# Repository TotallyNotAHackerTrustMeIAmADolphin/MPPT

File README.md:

# MPPT Controller - STM32F072 Firmware

A professional-grade firmware for a Maximum Power Point Tracking (MPPT) solar charge controller, optimized for the **ARM Cortex-M0** architecture. This project implements high-frequency power conversion with advanced sensing, robust safety, and optimized regulation logic.

---

## 🚀 Key Technical Features

### 1. High-Frequency PWM with Resolution Dithering
- **Frequency:** 200 kHz switching frequency for high power density.
- **Dithering:** Implements a **4-bit dithering table** (16 cycles). This effectively increases the PWM resolution from 240 steps to **3840 steps**, allowing for ultra-fine-grained voltage and current control.
- **Hardware Integration:** Managed via TIM1 with DMA-based automated duty cycle updates.

### 2. High-Performance Sensing (Ping-Pong ADC)
- **Zero-Latency DMA:** Uses circular DMA to sample 6 analog channels continuously.
- **Double Buffering:** Implements industry-standard **Ping-Pong buffering**. The CPU processes one half of the sample buffer while the DMA fills the other half, eliminating data tearing and race conditions.
- **Channels:** Input Voltage, Output Voltage, Input Current, Output Current, MOSFET Temperature, and MCU Internal Temperature.

### 3. Optimized Math Engine (Semantic Fixed-Point)
- **No FPU overhead:** Designed specifically for the STM32F0 (which lacks a hardware Floating Point Unit). All calculations use high-speed 32-bit and 64-bit integer arithmetic.
- **Unit Precision:** 
  - **Voltages:** Millivolts (`_mV`)
  - **Currents:** Milliamps (`_mA`)
  - **Power:** Microwatts (`_uW`)
  - **PWM:** Raw Dithered Ticks (`_ticks`)

### 4. Sunlight-Readable Telemetry Display
- **Hardware:** Integrated **Nokia 5110 (PCD8544)** LCD via SPI1.
- **Performance:** Non-blocking 10Hz UI refresh task decoupled from high-rate power control.
- **UI Design:** Real-time monitoring of Vin, Vout, Pout, and Operation Mode with vertical decimal alignment for high readability.

### 5. Advanced Control & Safety Logic
- **Velocity PI Regulation:** Implements a mathematically stable **Velocity PI algorithm** for Constant Voltage (CV) and Constant Current (CC) modes. This eliminates double-integration instability and provides rock-solid, ripple-free regulation.
- **Limit-Aware MPPT (P&O):** A refined Perturb & Observe algorithm with **power accumulation logic**. It accurately tracks the maximum power point on gentle slopes and intelligently "parks" the duty cycle near user limits to prevent state flapping.
- **Stabilized Global Sweep:** Slowed-down global sweep (15s duration) ensures hardware capacitors settle, providing a near-perfect MPP baseline without voltage offsets.
- **Hardware Safety Architecture:** Dedicated protection layer for the board:
  - **Over-Voltage:** 80V (Vin), 60V (Vout).
  - **Over-Current:** 20A (Input/Output).
  - **Under-Voltage:** 12.5V (Vin) floor to protect auxiliary power.
  - **Thermal:** 85°C internal limit.
  - **Reverse Flow:** Active backflow detection from battery to panel.

---

## 🛠 Hardware & Platform

### Board: openMPPT v1.1 (Custom Architecture)

- **MCU:** STM32F072RBT6 (ARM Cortex-M0 @ 48MHz).
- **Topology:** 4-Switch Synchronous Non-Inverting Buck-Boost.
- **Power Stage:** Four TI **CSD19505KCS** 80V N-Channel MOSFETs driven by two Infineon **IRS21867STRPBF** gate drivers. High-side drivers are powered by isolated **B1212S-1W** DC-DC converters for continuous high-voltage operation.
- **Sensing:** Precision zero-drift **INA240A4DR** current sense amplifiers. *(Note: Footprints for isolated ACS712 sensors exist as a planned future replacement for the INA240).*
- **Auxiliary Power:** **XL7005A** wide-input buck converters providing 12V and 3.3V logic rails from panel voltage.
- **Display:** Integrated **Nokia 5110 LCD** for real-time telemetry (SPI1).
- **Framework:** STM32Cube HAL.
- **Build System:** PlatformIO using a custom `openmppt` board definition.
- **Headless Operation:** The board regulates autonomously without requiring a serial connection.

---

## 🏗 Build & Development Workflow

### Requirements
- [PlatformIO Core](https://platformio.org/)
- STM32CubeMX (optional, for peripheral reconfiguration)

### Custom Build Automation
This project uses a custom script, `setup_cubemx_env_auto.py`, which bridges the gap between STM32CubeMX and PlatformIO.
- **Automatic Constant Extraction:** The script automatically reads your PWM frequency and timer settings directly from the `MPPT.ioc` file at compile-time.
- **Link Management:** Automatically handles library linking for USB and HAL drivers.

### Commands
```bash
# Build the firmware
pio run

# Upload via Black Magic Probe (standard in platformio.ini)
pio run -t upload

# Open the serial monitor (115200 baud)
pio device monitor
```

## 📈 Auto-Tuning
The firmware supports dynamic parameter tuning over serial. A Python script is provided to automate the finding of optimal MPPT parameters (aggressiveness, step sizes, and filtering) using a hybrid machine-learning approach.

```bash
# Install dependencies
pip install pyserial

# Run the tuner (Phase 1: Random Search, Phase 2: Local Fine-Tuning)
python scripts/tune_mppt.py --port /dev/ttyACM0
```

## 📐 Hardware Design
This repository includes all necessary design files for the MPPT controller hardware in the `hardware/` directory.

- **Schematics:** SVGs and PDFs available in `hardware/schematics/`.
- **PCB Design:** Gerbers, BOM, and Pick-and-Place files located in `hardware/PCB manufacturing/`.
- **3D Files:** STEP file for case/mechanical integration in `hardware/models/`.
- **Project Files:** EasyEDA source files in `hardware/EasyEDA/` and KiCad files in `hardware/KiCad/`.

---

## 🔗 Useful Links & Resources
- **Redirect printf to USB-VCP:** [Alexey Kosinov GitHub](https://github.com/alexeykosinov/Redirect-printf-to-USB-VCP-on-STM32H7-MCU)
- **How to use C++ with STM32 HAL:** [Bare Naked Embedded](https://barenakedembedded.com/how-to-use-cpp-with-stm32-hal/)
- **STM32 ADC Multiple Channels:** [Controllerstech](https://controllerstech.com/stm32-adc-multiple-channels/)
- **Send UART over USB:** [Controllerstech](https://controllerstech.com/send-and-receive-data-to-pc-without-uart-stm32-usb-com/)

---

## 📊 Telemetry & Debugging
Real-time telemetry and configuration are provided via **USB CDC (Virtual COM Port)**.

### 🌐 Web Dashboard
The easiest way to monitor and configure the controller is via the **Web Serial Dashboard**:
👉 **[Live Dashboard](https://totallynotahackertrustmeiamadolphin.github.io/MPPT/)**

*Requires a Chrome or Edge browser. Displays data in standard units (**V**, **A**, **W**) and features a robust settings synchronization mechanism.*

### Serial Protocol
The firmware emits machine-readable **JSON packets** with descriptive fault reporting:
- `Vin_mV / Vout_mV`: Input and Output Voltages.
- `Ain_mA / Aout_mA`: Input and Output Currents.
- `state`: IDLE, SWEEPING, MPPT, CV, CC, FAULT.
- `fault_reason`: Descriptive hardware error (e.g., `INPUT_UNDERVOLTAGE`).
- `duty_x100`: PWM duty cycle as a percentage with 0.01% precision.

---

## 📏 Development Conventions

- **Variable Naming:** Always include the unit suffix in variable names (e.g., `currentIn_mA`).
- **EEPROM Safety:** The board uses a **Signature Check** (`0xABCD`) to ensure safe defaults on first flash. PWM is automatically disabled during Flash writes to prevent controller crashes.
- **Integer Math:** Perform **multiplication before division** in all scaling logic to maintain precision. Avoid `float` and `double` at all costs.

---

## 📝 License
This project is licensed under the MIT License - see the [LICENSE](LICENSE) file for details.

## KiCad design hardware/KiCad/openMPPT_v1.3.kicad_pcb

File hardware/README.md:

# openMPPT Hardware Documentation

## ⚙️ Setup Requirements (per machine)
Before opening `hardware/KiCad/openMPPT_v1.3.kicad_pro`:
- **KiCad 10.0** — matches this project's file format (`generator_version "10.0"`); an older
  major version will prompt to upgrade the files.
- **Install the [`JLCPCB-Kicad-Library`](https://github.com/CDFER/JLCPCB-Kicad-Library) package**
  via KiCad's **Tools → Plugin and Content Manager**. This is the *official* PCM package — don't
  manually download/vendor a copy of it yourself, that's what causes the `KICAD8_3RD_PARTY`
  environment variable to stay unset and 3D models (switches, TVS diodes, generic passives -
  anything from the `PCM_JLCPCB` footprint library) to silently fail to render. Restart KiCad
  after installing so the variable takes effect.
- Everything else (the `easyeda2kicad`-sourced symbols/footprints/3D models for parts not on
  LCSC's basic-parts list) is already vendored in `hardware/KiCad/libraries/` and needs no setup.

## v1.3 Component Selection Summary
| Component | Part Number | Function | Rationale |
| :--- | :--- | :--- | :--- |
| Primary Buck IC | SCT2A25STER | 10V Aux Supply | High efficiency, 100V rating for 80V VIN |
| Logic Buck IC | SY8120B1ABC | 3.3V Logic Supply | Cascaded architecture for MCU safety |
| Power MOSFET | BSC030N08NS5 | Buck-Boost Stage | SMD (PG-TDSON-8-EP), 80V/100A, $R_{DS(on)}$ 3.0mΩ, $Q_g$ 76nC max |
| Bootstrap Diode | US1M | Gate Driver Supply | 1kV rating for transient protection |
| Gate-Off Diode | 1N4148W | MOSFET Turn-off | 4ns high-speed switching for low loss |
| Current Sensor | CC6937S8-3FB020 | Hall Effect Sensing | 3.3V compatible, isolated, 20A range |
| 10V TVS Diode | H12VH22U | Gate Drive Protection | 12V standoff, 6kW surge handled |
| 80V TVS Diode | 5.0SMDJ85CA | Main Rail Protection | 85V standoff, industrial 5kW capacity |

*(See `CALCULATIONS.typ` for full design justification and E24/E96 resistor value derivations.)*

## v1.1 Build Status: SUCCESS (Verified 2026-05-29)
The v1.1 PCB has been fully assembled and verified, v1.1 means the v1.0 but with some patches hand soldered to the board. However, several physical patches are required to achieve full functionality. These must be implemented in the next KiCad revision.

## 🛠 Critical Design Fixes (Implemented in v1.3)
- **Voltage Sensing**: Updated to **200k/4.7k** for 80V range.
- **Current Filter**: C10, C11 removed; moved to isolated **CC6937**.
- **Aux Power**: Replaced XL7005A with **SCT2A25/SY8120** cascaded setup.
- **Connectors**: Standardized on **Male XT60PW-M**.
- **Gate Drive**: Standardized on **5.1Ω** resistors with high-speed **1N4148W** bypass.
- **Protection**: TVS protection on the 80V main rail and 10V gate-drive rail. The 3.3V logic
  rail's originally-planned TVS (H3V3L06B, D9) was removed after datasheet verification showed
  it's an ESD-class part whose own clamping voltage exceeds the STM32's 4.0V absolute max at any
  current beyond a trivial ESD event — no purpose-built power-rail TVS clears 4.0V either (a
  physics limit of 3.3V-class parts). That rail's fault protection now rests on the SY8120B1's
  own regulation and the upstream Vin OV/UV limits already enforced in firmware.

## PCB Design Files
- **KiCad Source**: `hardware/KiCad/`
- **Production Files**: `hardware/PCB manufacturing/`
- **Vendored 3D Models/Symbols/Footprints**: `hardware/KiCad/libraries/easyeda2kicad/` (see
  "Setup Requirements" above for the one library that isn't vendored)

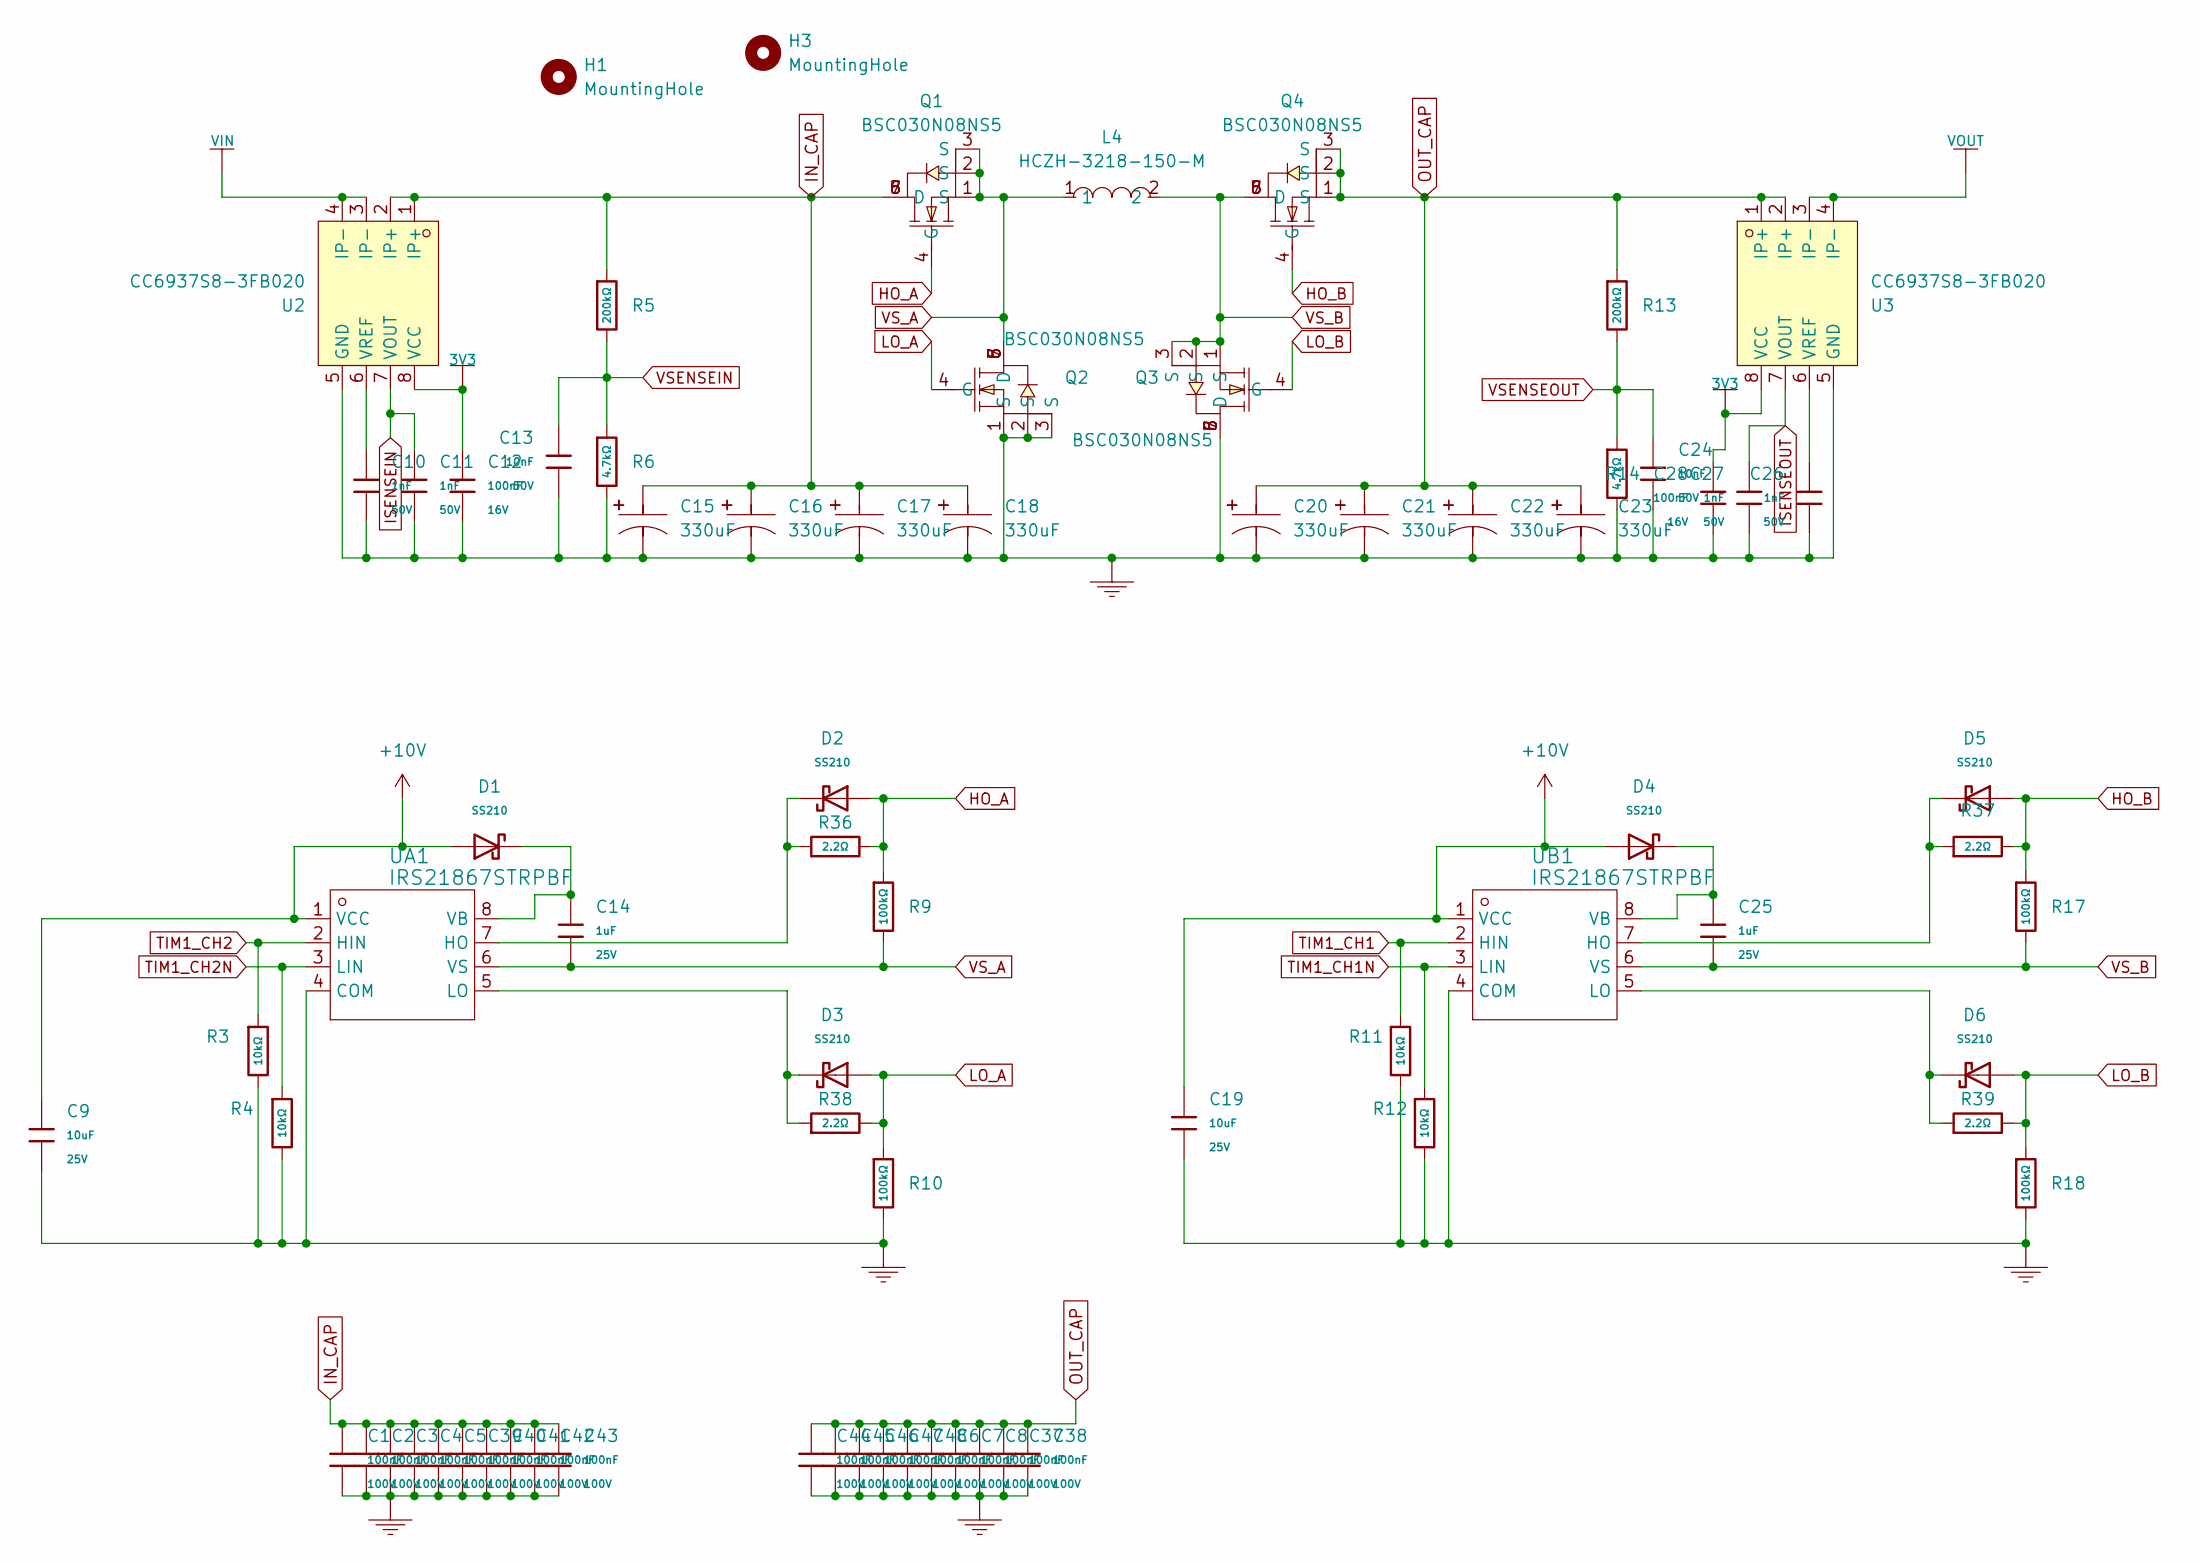
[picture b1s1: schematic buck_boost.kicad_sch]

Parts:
C1, C2, C3, C4, C5, C6, C7, C8, C37, C38, C39, C40, C41, C42, C43, C44, C45, C46, C47, C48: 100nF; C_0805; Voltage Rated 100V; Tolerance ±10%; Part CL21B104KCFNNNE; LCSC C28233
C9, C19: 10uF; C_0603; Voltage Rated 25V; Tolerance ±20%; Part CL10A106MA8NRNC; LCSC C96446
C10, C11, C26, C27: 1nF; C_0402; Voltage Rated 50V; Tolerance ±10%; Part 0402B102K500NT; LCSC C1523
C12, C28: 100nF; C_0402; Voltage Rated 16V; Tolerance ±10%; Part CL05B104KO5NNNC; LCSC C1525
C13, C24: 10nF; C_0402; Voltage Rated 50V; Tolerance ±10%; Part CL05B103KB5NNNC; LCSC C15195
C14, C25: 1uF; C_0402; Voltage Rated 25V; Tolerance ±10%; Part CL05A105KA5NQNC; LCSC C52923
C15, C16, C17, C18, C20, C21, C22, C23: 330uF; CAP-TH_BD12.5-P5.00-D0.6-FD; MPN LKML2502A331MF; LCSC Part C443153
D1, D2, D3, D4, D5, D6: SS210; D_SMA; Forward Voltage (Vf@If) 850mV@2A; Reverse Voltage (Vr) 100V; Part SS210; LCSC C14996
H1, H3: MountingHole; MountingHole_3.2mm_M3_DIN965
L4: HCZH-3218-150-M; IND-TH_L33.5-W23.0-P12.00_HCZH-3218; MPN HCZH-3218-150-M; LCSC Part C53699952
Q1, Q2, Q3, Q4: BSC030N08NS5; PG-TDSON-8_L5.0-W6.0-P1.27-BL-EP; MPN BSC030N08NS5; LCSC Part C501507
R3, R4, R11, R12: 10kΩ; R_0402; Overload Voltage (Max) 50V; Tolerance ±1%; Part 0402WGF1002TCE; LCSC C25744
R5, R13: 200kΩ; R_0603; Overload Voltage (Max) 75V; Tolerance ±1%; Part 0603WAF2003T5E; LCSC C25811
R6, R14: 4.7kΩ; R_0603; Overload Voltage (Max) 75V; Tolerance ±1%; Part 0603WAF4701T5E; LCSC C23162
R9, R10, R17, R18: 100kΩ; R_0603; Overload Voltage (Max) 75V; Tolerance ±1%; Part 0603WAF1003T5E; LCSC C25803
R36, R37, R38, R39: 2.2Ω; R_0603; Overload Voltage (Max) 75V; Tolerance ±1%; Part 0603WAF220KT5E; LCSC C22939
U2, U3: CC6937S8-3FB020; SOP-8_L4.9-W3.9-P1.27-LS6.0-BL; MPN CC6937S8-3FB020; LCSC Part C41421919
UA1: IRS21867STRPBF; SOIC-8_L5.0-W4.0-P1.27-LS6.0-BL; Manufacturer Part IRS21867STRPBF
UB1: IRS21867STRPBF; SOIC-8_L5.0-W4.0-P1.27-LS6.0-BL; Manufacturer Part IRS21867STRPBF

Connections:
3V3: C12.1, C28.1, U2.8 (VCC), U3.8 (VCC); also elsewhere on the board
+10V: C9.1, C19.1, D1.2, D4.2, UA1.1 (VCC), UB1.1 (VCC); also elsewhere on the board
GND: C1.2, C2.2, C3.2, C4.2, C5.2, C6.2, C7.2, C8.2, C9.2, C10.2, C11.2, C12.2, C13.2, C15.2 (-), C16.2 (-), C17.2 (-), C18.2 (-), C19.2, C20.2 (-), C21.2 (-), C22.2 (-), C23.2 (-), C24.2, C26.2, C27.2, C28.2, C37.2, C38.2, C39.2, C40.2, C41.2, C42.2, C43.2, C44.2, C45.2, C46.2, C47.2, C48.2, Q2.1 (S), Q2.2 (S), Q2.3 (S), Q3.5 (D), Q3.6 (D), Q3.7 (D), Q3.8 (D), R3.2, R4.2, R6.2, R10.2, R11.2, R12.2, R14.2, R18.2, U2.5 (GND), U3.5 (GND), UA1.4 (COM), UB1.4 (COM); also elsewhere on the board
HO_A: D2.2, Q1.4 (G), R9.1, R36.2
HO_B: D5.2, Q4.4 (G), R17.1, R37.2
IN_CAP: C1.1, C2.1, C3.1, C4.1, C5.1, C15.1 (+), C16.1 (+), C17.1 (+), C18.1 (+), C39.1, C40.1, C41.1, C42.1, C43.1, Q1.5 (D), Q1.6 (D), Q1.7 (D), Q1.8 (D), R5.1, U2.1 (IP+), U2.2 (IP+)
ISENSEIN: C11.1, U2.7 (VOUT); also elsewhere on the board
ISENSEOUT: C27.1, U3.7 (VOUT); also elsewhere on the board
LO_A: D3.2, Q2.4 (G), R10.1, R38.2
LO_B: D6.2, Q3.4 (G), R18.1, R39.2
unnamed: C10.1, U2.6 (VREF)
unnamed: C26.1, U3.6 (VREF)
unnamed: D2.1, R36.1, UA1.7 (HO)
unnamed: D3.1, R38.1, UA1.5 (LO)
unnamed: C14.1, D1.1, UA1.8 (VB)
unnamed: D5.1, R37.1, UB1.7 (HO)
unnamed: D6.1, R39.1, UB1.5 (LO)
unnamed: C25.1, D4.1, UB1.8 (VB)
OUT_CAP: C6.1, C7.1, C8.1, C20.1 (+), C21.1 (+), C22.1 (+), C23.1 (+), C37.1, C38.1, C44.1, C45.1, C46.1, C47.1, C48.1, Q4.1 (S), Q4.2 (S), Q4.3 (S), R13.1, U3.1 (IP+), U3.2 (IP+)
TIM1_CH1: R11.1, UB1.2 (HIN); also elsewhere on the board
TIM1_CH1N: R12.1, UB1.3 (LIN); also elsewhere on the board
TIM1_CH2: R3.1, UA1.2 (HIN); also elsewhere on the board
TIM1_CH2N: R4.1, UA1.3 (LIN); also elsewhere on the board
VIN: U2.3 (IP-), U2.4 (IP-); also elsewhere on the board
VOUT: U3.3 (IP-), U3.4 (IP-); also elsewhere on the board
VSENSEIN: C13.1, R5.2, R6.1; also elsewhere on the board
VSENSEOUT: C24.1, R13.2, R14.1; also elsewhere on the board
VS_A: C14.2, L4.1, Q1.1 (S), Q1.2 (S), Q1.3 (S), Q2.5 (D), Q2.6 (D), Q2.7 (D), Q2.8 (D), R9.2, UA1.6 (VS)
VS_B: C25.2, L4.2, Q3.1 (S), Q3.2 (S), Q3.3 (S), Q4.5 (D), Q4.6 (D), Q4.7 (D), Q4.8 (D), R17.2, UB1.6 (VS)

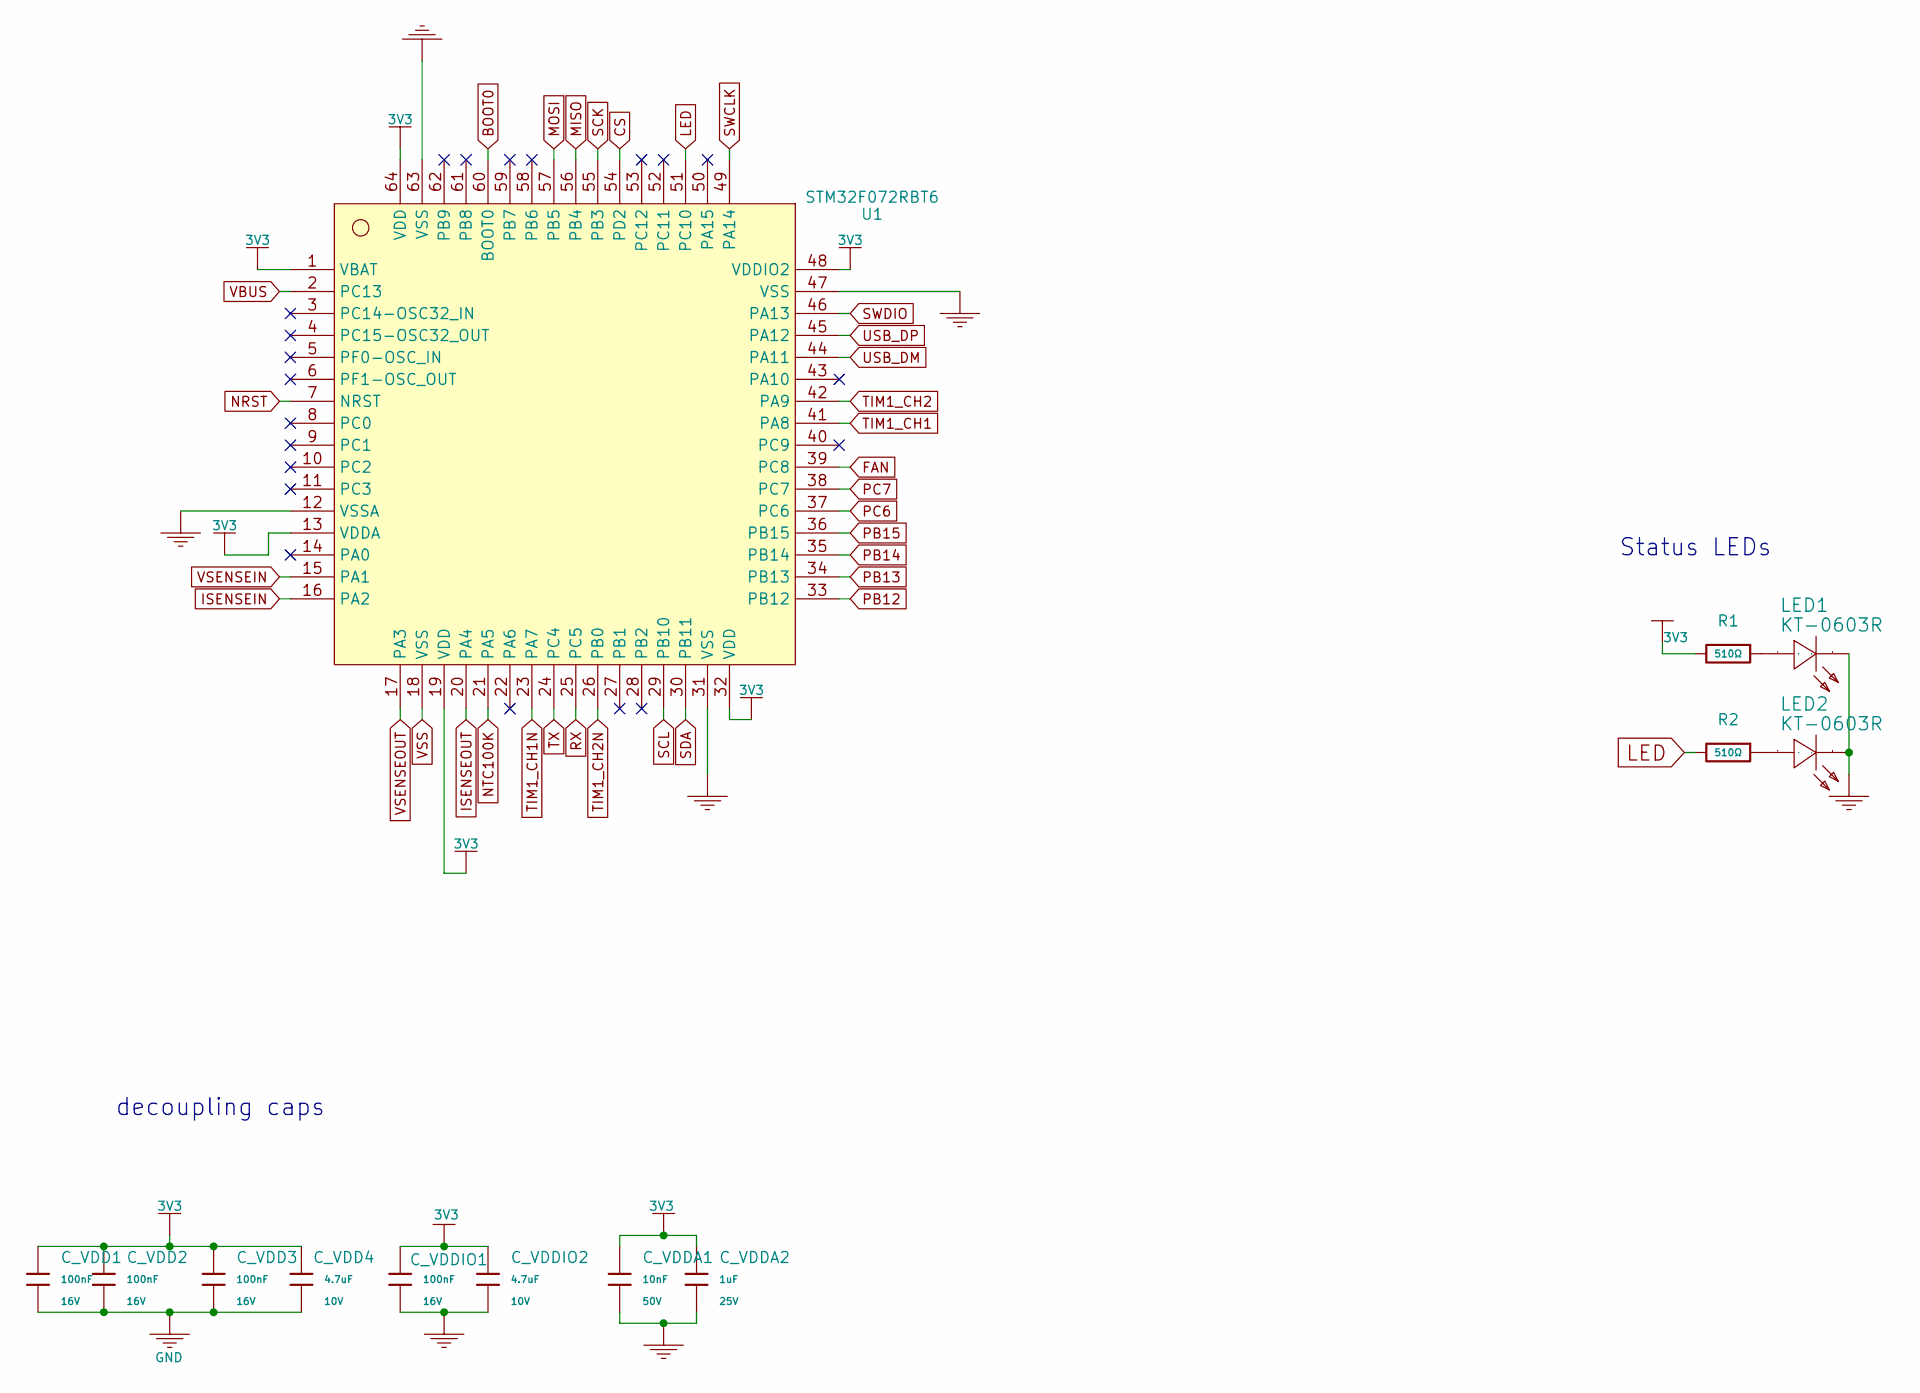
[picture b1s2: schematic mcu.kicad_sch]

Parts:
C_VDD1, C_VDD2, C_VDD3: 100nF; C_0402; Voltage Rated 16V; Tolerance ±10%; Part CL05B104KO5NNNC; LCSC C1525
C_VDD4: 4.7uF; C_0402; Voltage Rated 10V; Tolerance ±20%; Part CL05A475MP5NRNC; LCSC C23733
C_VDDA1: 10nF; C_0402; Voltage Rated 50V; Tolerance ±10%; Part CL05B103KB5NNNC; LCSC C15195
C_VDDA2: 1uF; C_0402; Voltage Rated 25V; Tolerance ±10%; Part CL05A105KA5NQNC; LCSC C52923
C_VDDIO1: 100nF; C_0402; Voltage Rated 16V; Tolerance ±10%; Part CL05B104KO5NNNC; LCSC C1525
C_VDDIO2: 4.7uF; C_0402; Voltage Rated 10V; Tolerance ±20%; Part CL05A475MP5NRNC; LCSC C23733
LED1, LED2: KT-0603R; LED_0603_1608Metric; Manufacturer Part KT-0603R
R1, R2: 510Ω; R_0402; Overload Voltage (Max) 50V; Tolerance ±1%; Part 0402WGF5100TCE; LCSC C25123
U1: STM32F072RBT6; LQFP-64_L10.0-W10.0-P0.50-LS12.0-BL; MPN STM32F072RBT6; LCSC Part C46046

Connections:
3V3: C_VDD1.1, C_VDD2.1, C_VDD3.1, C_VDD4.1, C_VDDA1.1, C_VDDA2.1, C_VDDIO1.1, C_VDDIO2.1, R1.2, U1.1 (VBAT), U1.13 (VDDA), U1.19 (VDD), U1.32 (VDD), U1.48 (VDDIO2), U1.64 (VDD); also elsewhere on the board
BOOT0: U1.60 (BOOT0); also elsewhere on the board
CS: U1.54 (PD2); also elsewhere on the board
FAN: U1.39 (PC8); also elsewhere on the board
GND: C_VDD1.2, C_VDD2.2, C_VDD3.2, C_VDD4.2, C_VDDA1.2, C_VDDA2.2, C_VDDIO1.2, C_VDDIO2.2, LED1.1 (K), LED2.1 (K), U1.12 (VSSA), U1.31 (VSS), U1.47 (VSS), U1.63 (VSS); also elsewhere on the board
ISENSEIN: U1.16 (PA2); also elsewhere on the board
ISENSEOUT: U1.20 (PA4); also elsewhere on the board
LED: R2.2, U1.51 (PC10)
MISO: U1.56 (PB4); also elsewhere on the board
MOSI: U1.57 (PB5); also elsewhere on the board
NRST: U1.7 (NRST); also elsewhere on the board
NTC100K: U1.21 (PA5); also elsewhere on the board
unnamed: LED1.2 (A), R1.1
unnamed: LED2.2 (A), R2.1
PB12: U1.33 (PB12); also elsewhere on the board
PB13: U1.34 (PB13); also elsewhere on the board
PB14: U1.35 (PB14); also elsewhere on the board
PB15: U1.36 (PB15); also elsewhere on the board
PC6: U1.37 (PC6); also elsewhere on the board
PC7: U1.38 (PC7); also elsewhere on the board
RX: U1.25 (PC5); also elsewhere on the board
SCK: U1.55 (PB3); also elsewhere on the board
SCL: U1.29 (PB10); also elsewhere on the board
SDA: U1.30 (PB11); also elsewhere on the board
SWCLK: U1.49 (PA14); also elsewhere on the board
SWDIO: U1.46 (PA13); also elsewhere on the board
TIM1_CH1: U1.41 (PA8); also elsewhere on the board
TIM1_CH1N: U1.23 (PA7); also elsewhere on the board
TIM1_CH2: U1.42 (PA9); also elsewhere on the board
TIM1_CH2N: U1.26 (PB0); also elsewhere on the board
TX: U1.24 (PC4); also elsewhere on the board
USB_DM: U1.44 (PA11); also elsewhere on the board
USB_DP: U1.45 (PA12); also elsewhere on the board
VBUS: U1.2 (PC13); also elsewhere on the board
VSENSEIN: U1.15 (PA1); also elsewhere on the board
VSENSEOUT: U1.17 (PA3); also elsewhere on the board
VSS: U1.18 (VSS)

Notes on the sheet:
Status LEDs
decoupling caps

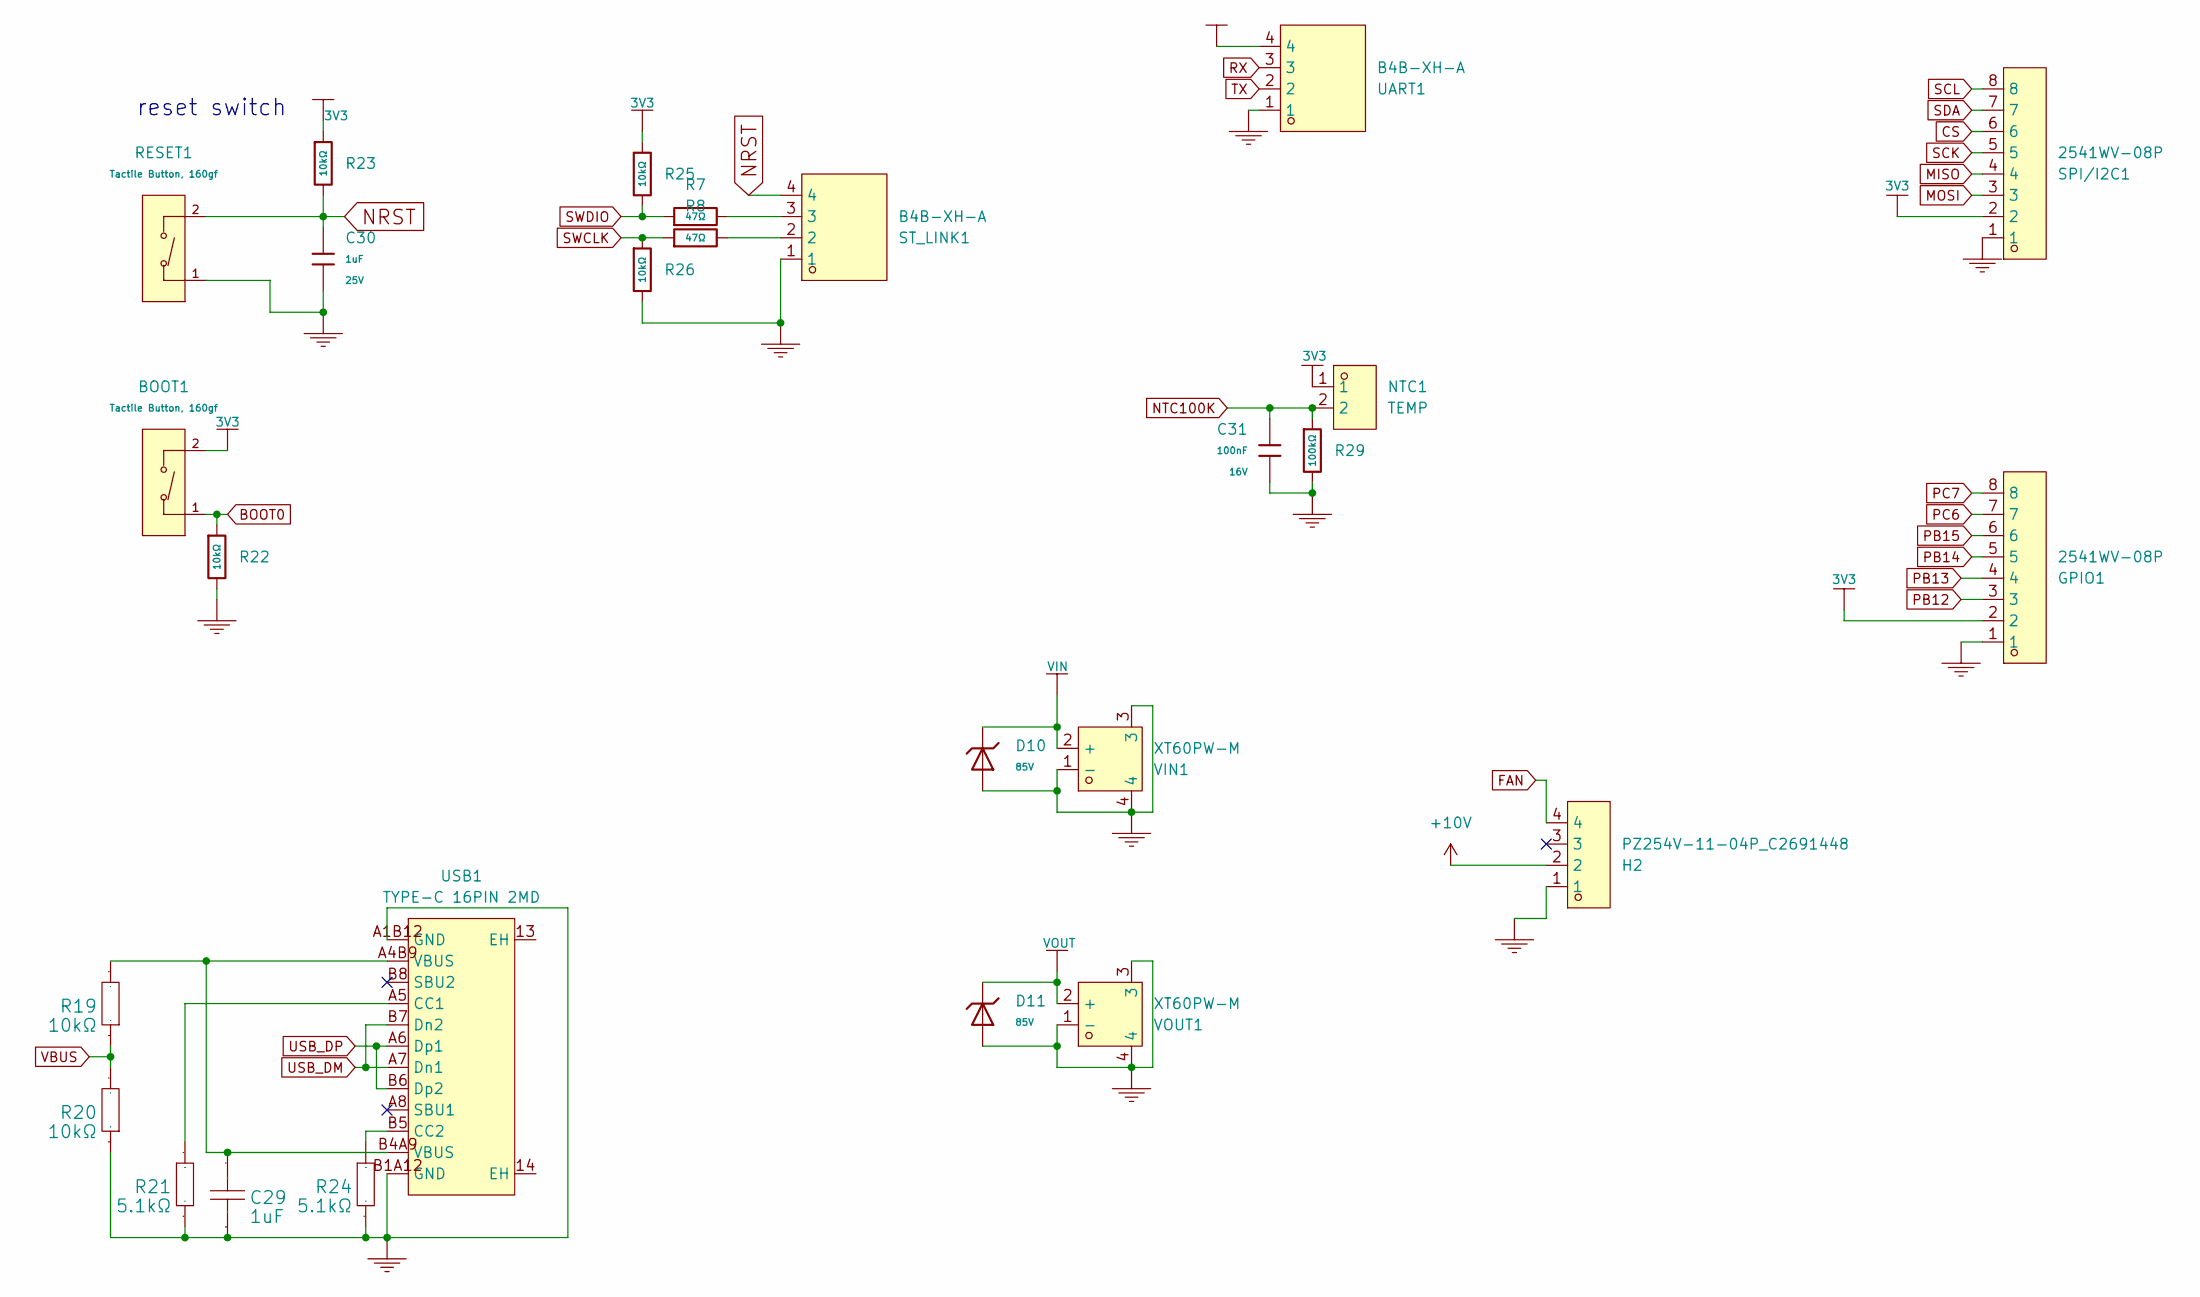
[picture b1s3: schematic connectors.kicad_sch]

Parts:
BOOT1: Tactile Button, 160gf; SW_TS-1088-AR02016; Voltage Rating (Dc) 12V; Part TS-1088-AR02016; LCSC C720477
C29: 1uF; C_0402_1005Metric; Manufacturer Part CL05A105KA5NQNC
C30: 1uF; C_0402; Voltage Rated 25V; Tolerance ±10%; Part CL05A105KA5NQNC; LCSC C52923
C31: 100nF; C_0402; Voltage Rated 16V; Tolerance ±10%; Part CL05B104KO5NNNC; LCSC C1525
D10, D11: 85V; D_SMC; Clamping Voltage 137V; Voltage - Breakdown 104V; Part 5.0SMDJ85CA; LCSC C42394457
GPIO1: 2541WV-08P; HDR-TH_8P-P2.54-V-M-4; MPN 2541WV-08P; LCSC Part C5383116
H2: PZ254V-11-04P_C2691448; HDR-TH_4P-P2.54-V-M; MPN PZ254V-11-04P; LCSC Part C2691448
NTC1: TEMP; HDR-TH_2P-P2.54-V-M; MPN PZ254V-11-02P; LCSC Part C492401
R7, R8: 47Ω; R_0603; Overload Voltage (Max) 75V; Tolerance ±1%; Part 0603WAF470JT5E; LCSC C23182
R19, R20: 10kΩ; R_0402_1005Metric; Manufacturer Part 0402WGF1002TCE
R21, R24: 5.1kΩ; R_0402_1005Metric; Manufacturer Part 0402WGF5101TCE
R22, R23, R25, R26: 10kΩ; R_0402; Overload Voltage (Max) 50V; Tolerance ±1%; Part 0402WGF1002TCE; LCSC C25744
R29: 100kΩ; R_0402; Overload Voltage (Max) 50V; Tolerance ±1%; Part 0402WGF1003TCE; LCSC C25741
RESET1: Tactile Button, 160gf; SW_TS-1088-AR02016; Voltage Rating (Dc) 12V; Part TS-1088-AR02016; LCSC C720477
SPI/I2C1: 2541WV-08P; HDR-TH_8P-P2.54-V-M-4; MPN 2541WV-08P; LCSC Part C5383116
ST_LINK1: B4B-XH-A; CONN-TH_B4B-XH-A-LF-SN; MPN B4B-XH-A(LF)(SN); LCSC Part C144395
UART1: B4B-XH-A; CONN-TH_B4B-XH-A-LF-SN; MPN B4B-XH-A(LF)(SN); LCSC Part C144395
USB1: TYPE-C 16PIN 2MD; USB-C-SMD_TYPE-C-16PIN-2MD-073; MPN TYPE-C 16PIN 2MD(073); LCSC Part C2765186
VIN1: XT60PW-M; CONN-TH_XT60PW-M; MPN XT60PW-M; LCSC Part C98732
VOUT1: XT60PW-M; CONN-TH_XT60PW-M; MPN XT60PW-M; LCSC Part C98732

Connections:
3V3: BOOT1.2 (B), GPIO1.2, NTC1.1, R23.1, R25.1, SPI/I2C1.2, UART1.4; also elsewhere on the board
+10V: H2.2; also elsewhere on the board
BOOT0: BOOT1.1 (A), R22.1; also elsewhere on the board
CS: SPI/I2C1.6; also elsewhere on the board
FAN: H2.4; also elsewhere on the board
GND: C29.1, C30.2, C31.2, D10.2, D11.2, GPIO1.1, H2.1, R20.1, R21.2, R22.2, R24.2, R26.2, R29.2, RESET1.1 (A), SPI/I2C1.1, ST_LINK1.1, UART1.1, USB1.A1B12 (GND), USB1.B1A12 (GND), VIN1.1 (-), VIN1.3, VIN1.4, VOUT1.1 (-), VOUT1.3, VOUT1.4; also elsewhere on the board
MISO: SPI/I2C1.4; also elsewhere on the board
MOSI: SPI/I2C1.3; also elsewhere on the board
NRST: C30.1, R23.2, RESET1.2 (B), ST_LINK1.4; also elsewhere on the board
NTC100K: C31.1, NTC1.2, R29.1; also elsewhere on the board
unnamed: C29.2, R19.2, USB1.A4B9 (VBUS), USB1.B4A9 (VBUS)
unnamed: R7.2, ST_LINK1.3
unnamed: R8.2, ST_LINK1.2
unnamed: R21.1, USB1.A5 (CC1)
unnamed: R24.1, USB1.B5 (CC2)
PB12: GPIO1.3; also elsewhere on the board
PB13: GPIO1.4; also elsewhere on the board
PB14: GPIO1.5; also elsewhere on the board
PB15: GPIO1.6; also elsewhere on the board
PC6: GPIO1.7; also elsewhere on the board
PC7: GPIO1.8; also elsewhere on the board
RX: UART1.3; also elsewhere on the board
SCK: SPI/I2C1.5; also elsewhere on the board
SCL: SPI/I2C1.8; also elsewhere on the board
SDA: SPI/I2C1.7; also elsewhere on the board
SWCLK: R8.1, R26.1; also elsewhere on the board
SWDIO: R7.1, R25.2; also elsewhere on the board
TX: UART1.2; also elsewhere on the board
USB_DM: USB1.A7 (Dn1), USB1.B7 (Dn2); also elsewhere on the board
USB_DP: USB1.A6 (Dp1), USB1.B6 (Dp2); also elsewhere on the board
VBUS: R19.1, R20.2; also elsewhere on the board
VIN: D10.1, VIN1.2 (+); also elsewhere on the board
VOUT: D11.1, VOUT1.2 (+); also elsewhere on the board

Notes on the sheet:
reset switch

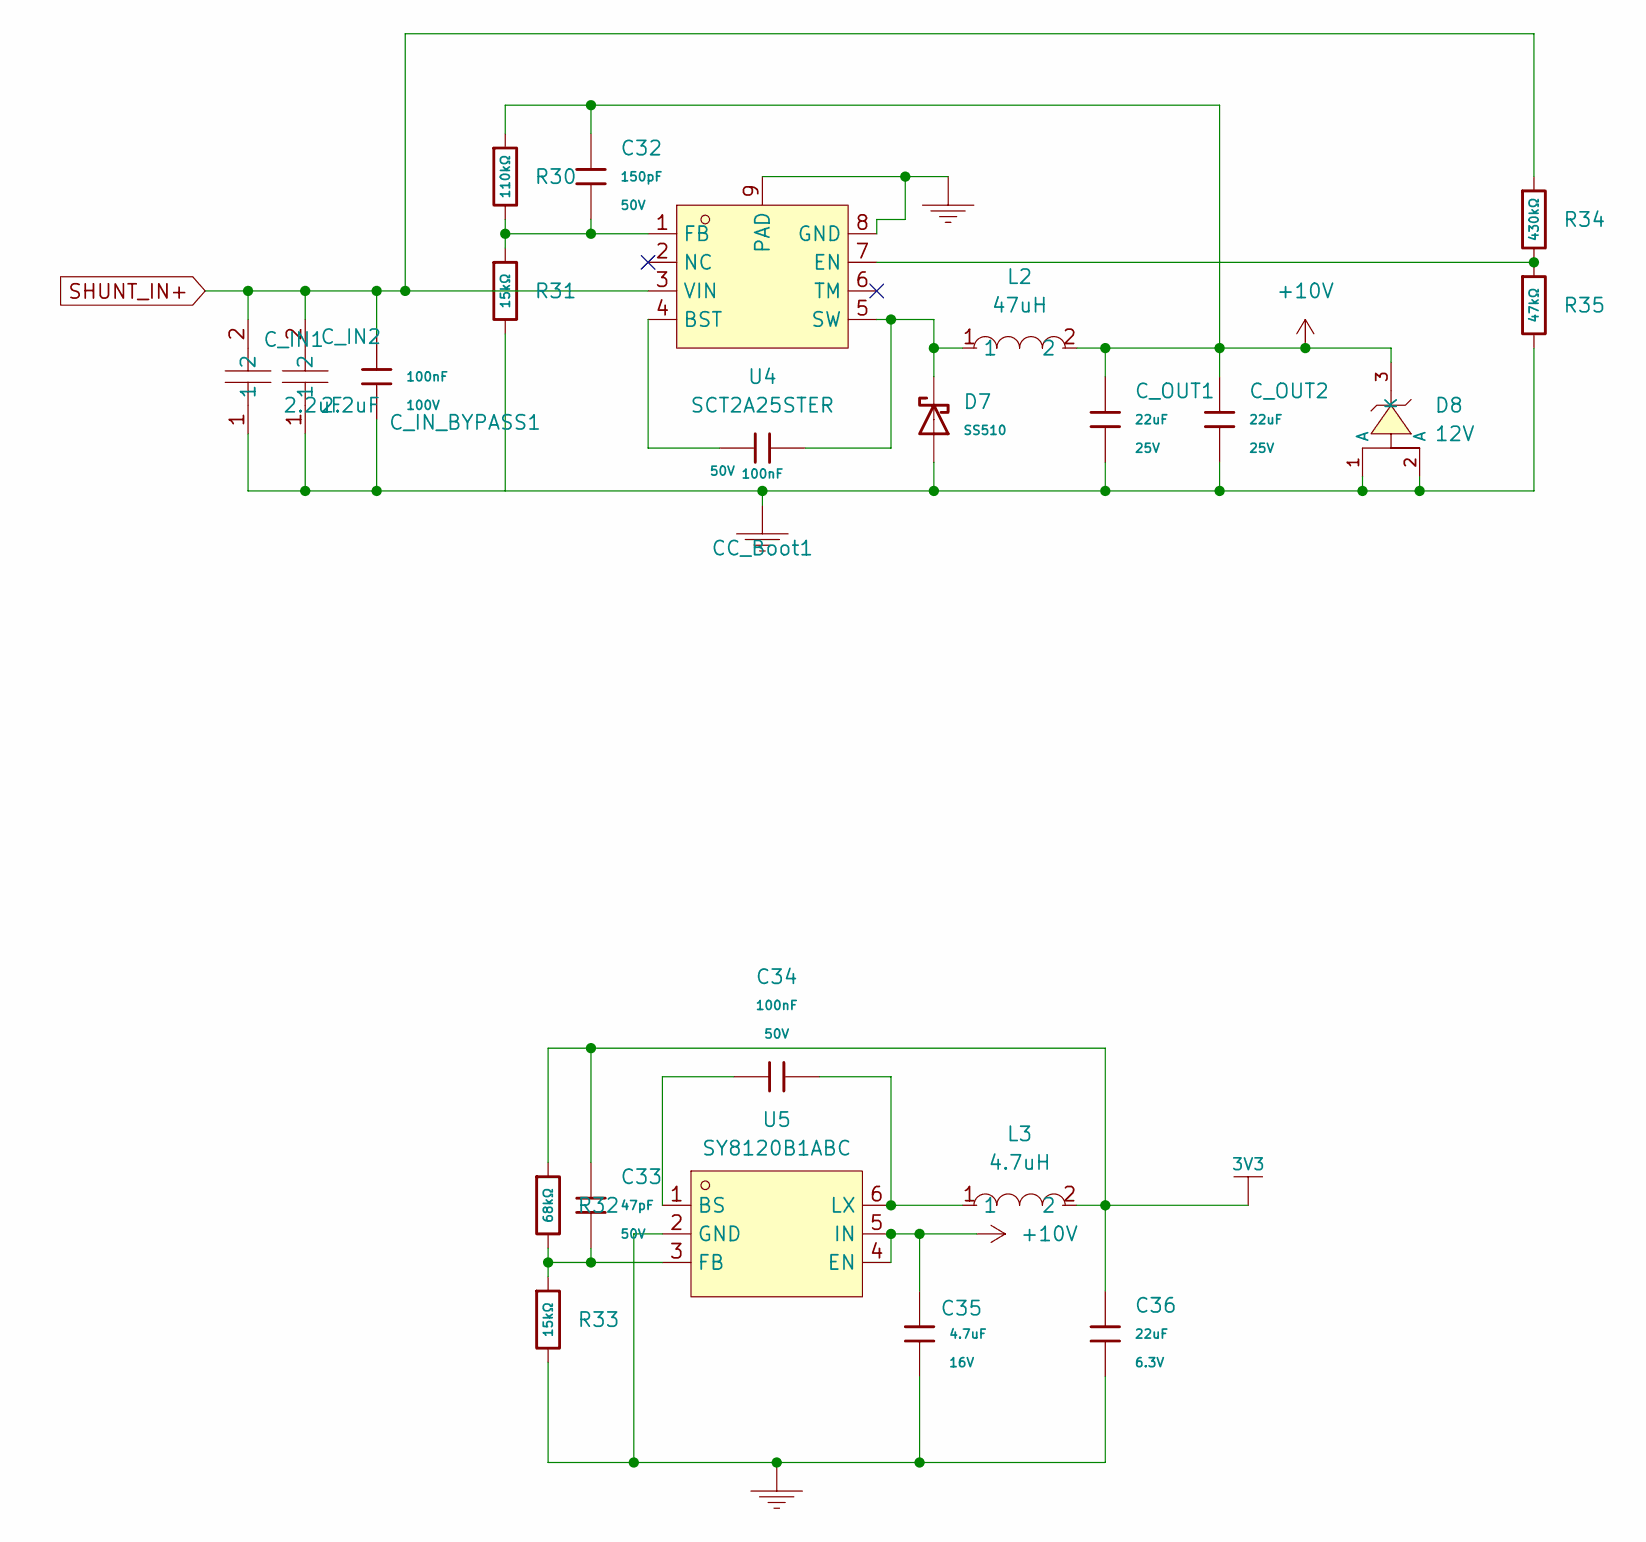
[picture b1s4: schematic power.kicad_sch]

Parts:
C32: 150pF; C_0603; Voltage Rated 50V; Tolerance ±10%; Part 0603B151K500NT; LCSC C1594
C33: 47pF; C_0603; Voltage Rated 50V; Tolerance ±5%; Part CL10C470JB8NNNC; LCSC C1671
C34: 100nF; C_0603; Voltage Rated 50V; Tolerance ±10%; Part CC0603KRX7R9BB104; LCSC C14663
C35: 4.7uF; C_0603; Voltage Rated 16V; Tolerance ±10%; Part CL10A475KO8NNNC; LCSC C19666
C36: 22uF; C_0603; Voltage Rated 6.3V; Tolerance ±20%; Part CL10A226MQ8NRNC; LCSC C59461
CC_Boot1: 100nF; C_0603; Voltage Rated 50V; Tolerance ±10%; Part CC0603KRX7R9BB104; LCSC C14663
C_IN1, C_IN2: 2.2uF; C1210; MPN TCC1210X7R225K101MT; LCSC Part C5449052
C_IN_BYPASS1: 100nF; C_0805; Voltage Rated 100V; Tolerance ±10%; Part CL21B104KCFNNNE; LCSC C28233
C_OUT1, C_OUT2: 22uF; C_0805; Voltage Rated 25V; Tolerance ±20%; Part CL21A226MAQNNNE; LCSC C45783
D7: SS510; D_SMA; Forward Voltage (Vf@If) 850mV@5A; Reverse Voltage (Vr) 100V; Part SS510; LCSC C7420368
D8: 12V; DFN2020-3_L2.0-W2.0-P0.65-BR-1; Part H12VH22U; LCSC C20615799
L2: 47uH; IND-SMD_L12.5-W12.5-1; MPN GXDR1207-470MT; LCSC Part C52196367
L3: 4.7uH; IND-SMD_L2.0-W1.6-B; MPN FTC201610S4R7MBCA; LCSC Part C5832346
R30: 110kΩ; R_0603; Overload Voltage (Max) 75V; Tolerance ±1%; Part 0603WAF1103T5E; LCSC C25805
R31, R33: 15kΩ; R_0603; Overload Voltage (Max) 75V; Tolerance ±1%; Part 0603WAF1502T5E; LCSC C22809
R32: 68kΩ; R_0603; Overload Voltage (Max) 75V; Tolerance ±1%; Part 0603WAF6802T5E; LCSC C23231
R34: 430kΩ; R_0603; Overload Voltage (Max) 75V; Tolerance ±1%; Part 0603WAF4303T5E; LCSC C25969
R35: 47kΩ; R_0603; Overload Voltage (Max) 75V; Tolerance ±1%; Part 0603WAF4702T5E; LCSC C25819
U4: SCT2A25STER; ESOP-8_L4.9-W3.9-P1.27-LS6.0-BL-EP; MPN SCT2A25STER; LCSC Part C5124114
U5: SY8120B1ABC; SOT-23-6_L2.9-W1.6-P0.95-LS2.8-BL; MPN SY8120B1ABC; LCSC Part C88474

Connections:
3V3: C33.1, C36.1, L3.2, R32.1; also elsewhere on the board
+10V: C32.1, C35.1, C_OUT1.1, C_OUT2.1, D8.3 (K), L2.2, R30.1, U5.4 (EN), U5.5 (IN); also elsewhere on the board
GND: C35.2, C36.2, C_IN1.1, C_IN2.1, C_IN_BYPASS1.2, C_OUT1.2, C_OUT2.2, D7.2, D8.1 (A), D8.2 (A), R33.2, R35.2, U4.8 (GND), U4.9 (PAD), U5.2 (GND); also elsewhere on the board
unnamed: CC_Boot1.1, U4.4 (BST)
unnamed: R34.2, R35.1, U4.7 (EN)
unnamed: C32.2, R30.2, R31.1, U4.1 (FB)
unnamed: CC_Boot1.2, D7.1, L2.1, U4.5 (SW)
unnamed: C34.1, U5.1 (BS)
unnamed: C33.2, R32.2, R33.1, U5.3 (FB)
unnamed: C34.2, L3.1, U5.6 (LX)
SHUNT_IN+: C_IN1.2, C_IN2.2, C_IN_BYPASS1.1, R34.1, U4.3 (VIN)
